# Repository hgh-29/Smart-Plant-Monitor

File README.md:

[README.pdf](https://github.com/user-attachments/files/24240184/README.pdf)

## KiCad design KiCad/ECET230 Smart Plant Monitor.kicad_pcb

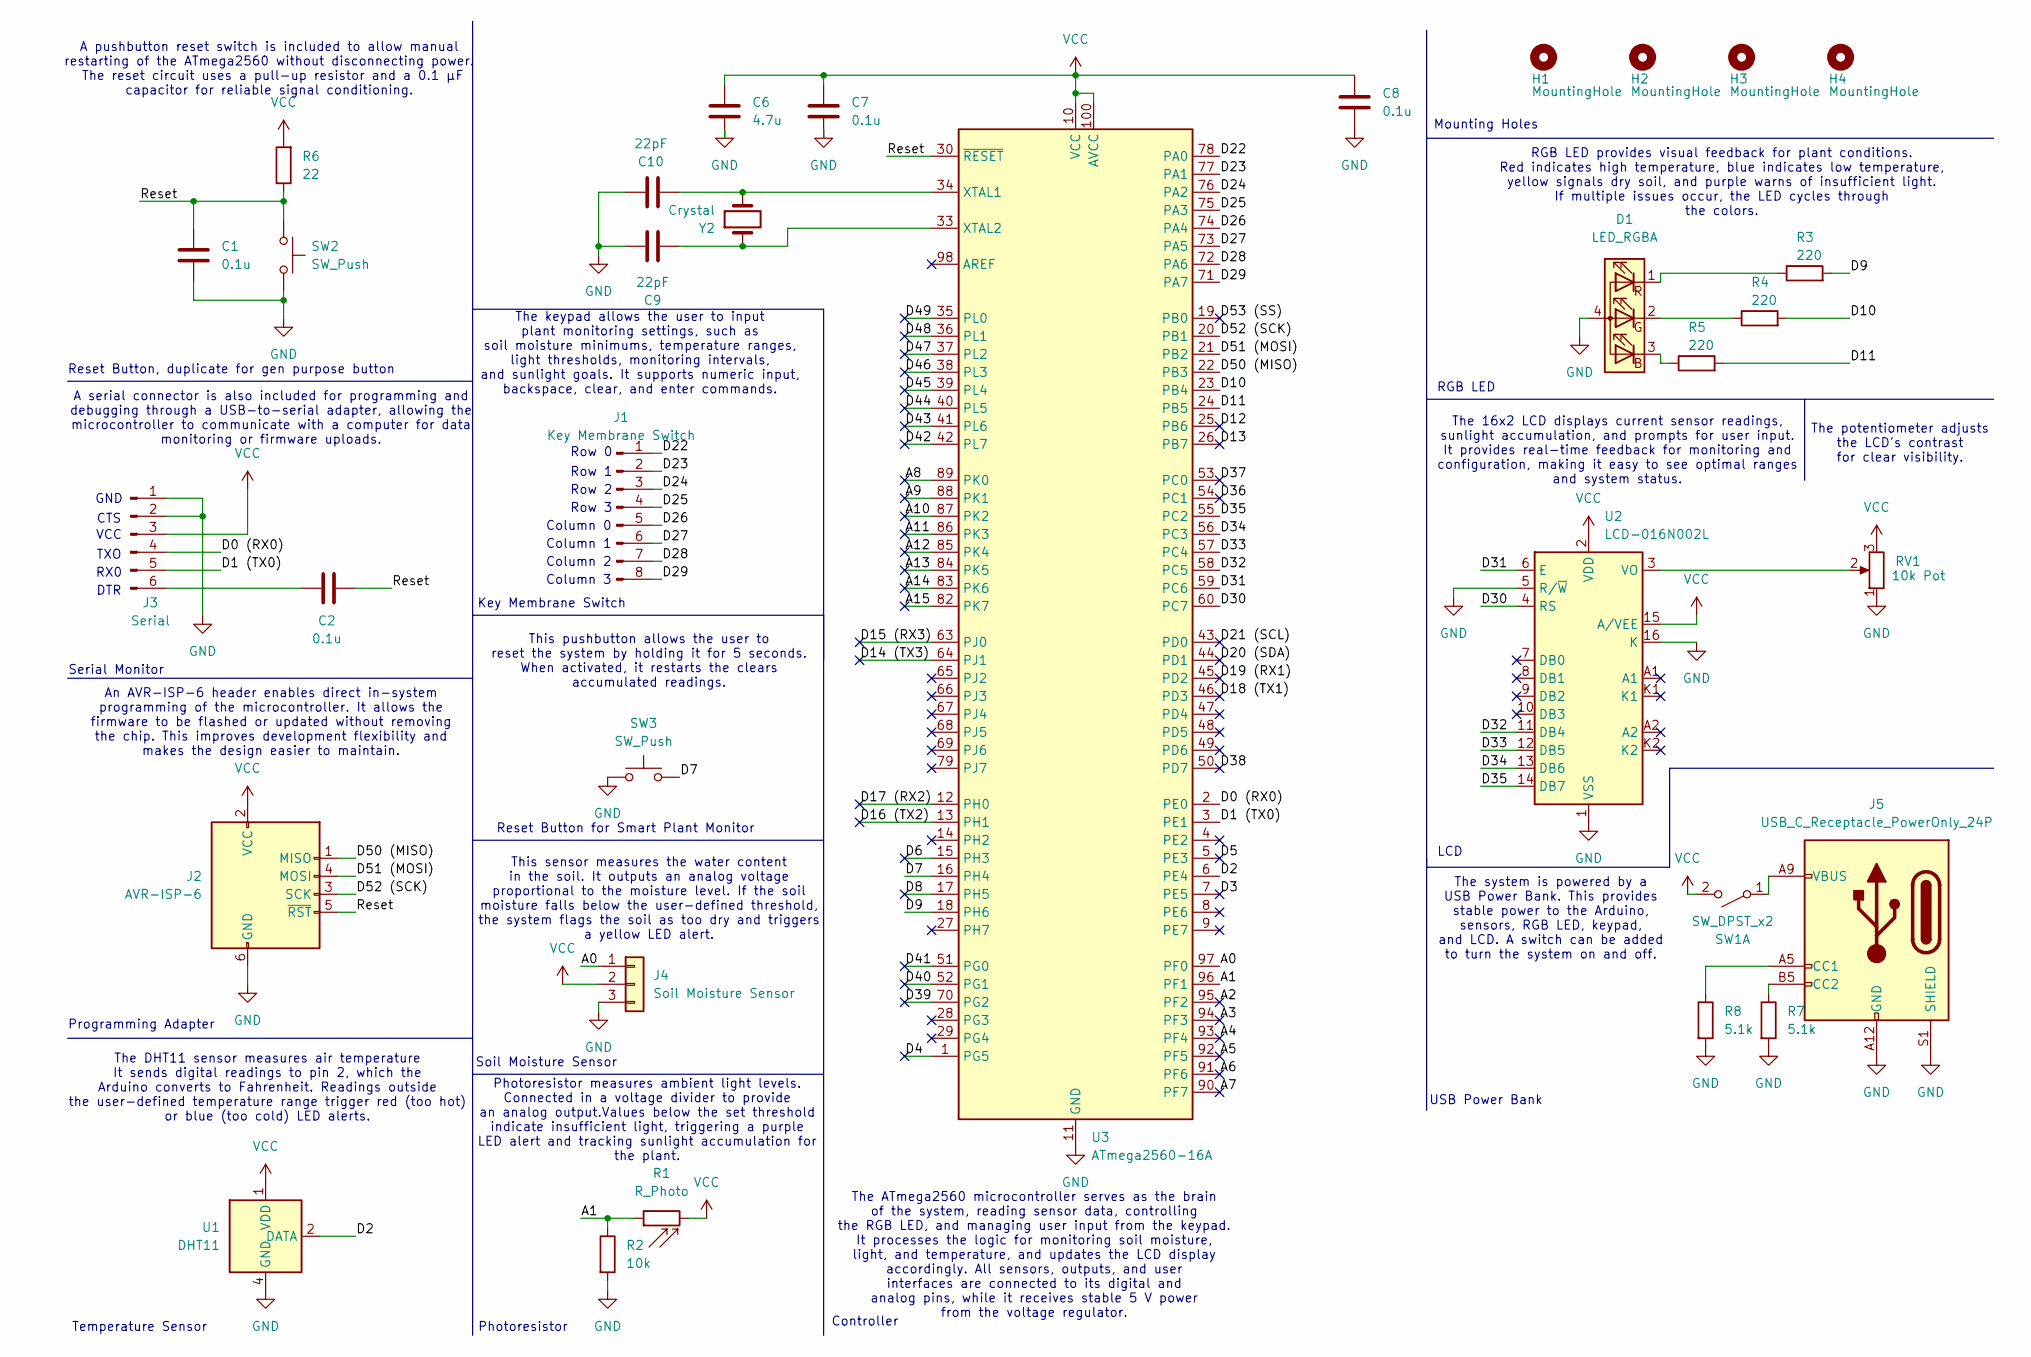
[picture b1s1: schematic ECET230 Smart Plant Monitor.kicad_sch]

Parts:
C1, C2, C7, C8: 0.1u; CP_Elec_3x5.3; MPN GRM033C71C104KE14D
C6: 4.7u; CP_Elec_3x5.3; MPN GRM035R60J475ME15D
C9, C10: 22pF; CP_Elec_3x5.3; MPN C0603C220J5GACTU
D1: LED_RGBA; LED_RGB_5050-6; MPN YSL-R596CR3G4B5C-C10
H1, H2, H3, H4: MountingHole; MountingHole_2.1mm
J1: Key Membrane Switch; PinHeader_1x08_P1.00mm_Vertical; MPN PPTC081LFBN-RC
J2: AVR-ISP-6; Tag-Connect_TC2030-IDC-FP_2x03_P1.27mm_Vertical; MPN SFH11-NBPC-D03-ST-BK
J3: Serial; PinSocket_1x06_P1.00mm_Vertical_SMD_Pin1Right; MPN OSTOQ063250
J4: Soil Moisture Sensor; PinSocket_1x03_P2.54mm_Horizontal; MPN PPPC031LGBN-RC
J5: USB_C_Receptacle_PowerOnly_24P; USB_C_Receptacle_GCT_USB4085; MPN USB4125-GF-A
R1: R_Photo; R_Axial_DIN0309_L9.0mm_D3.2mm_P12.70mm_Horizontal; MPN PDV-P8103
R2: 10k; R_Axial_DIN0309_L9.0mm_D3.2mm_P12.70mm_Horizontal; MPN CF14JT10K0
R3, R4, R5: 220; R_Axial_DIN0309_L9.0mm_D3.2mm_P12.70mm_Horizontal; MPN CF14JT220R
R6: 22; R_Axial_DIN0207_L6.3mm_D2.5mm_P10.16mm_Horizontal; MPN CF14JT22R0
R7, R8: 5.1k; R_Axial_DIN0207_L6.3mm_D2.5mm_P10.16mm_Horizontal; MPN CF14JT5K10
RV1: 10k Pot; Potentiometer_Bourns_3266P_Horizontal; MPN PV36W103C01B00
SW1: SW_DPST_x2; SW_DIP_SPSTx01_Slide_Copal_CHS-01A_W5.08mm_P1.27mm_JPin; MPN JS202011CQN
SW2, SW3: SW_Push; SW_PUSH-12mm_Wuerth-430476085716; MPN Y41A00521FPLFS
U1: DHT11; Aosong_DHT11_5.5x12.0_P2.54mm; MPN 386
U2: LCD-016N002L; MPN HD44780U (LCD-II)
U3: ATmega2560-16A; TQFP-100_14x14mm_P0.5mm; MPN ATMEGA2560-16AU
Y2: Crystal; Crystal_AT310_D3.0mm_L10.0mm_Horizontal; MPN ABS07-32.768KHZ-T

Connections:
/A0: J4.1, U3.97 (PF0)
/A1: R1.1, R2.1, U3.96 (PF1)
/A2: U3.95 (PF2)
/A3: U3.94 (PF3)
/A4: U3.93 (PF4)
/A5: U3.92 (PF5)
/A6: U3.91 (PF6)
/A7: U3.90 (PF7)
/A8: U3.89 (PK0)
/A9: U3.88 (PK1)
/A10: U3.87 (PK2)
/A11: U3.86 (PK3)
/A12: U3.85 (PK4)
/A13: U3.84 (PK5)
/A14: U3.83 (PK6)
/A15: U3.82 (PK7)
/D0 (RX0): J3.4, U3.2 (PE0)
/D1 (TX0): J3.5, U3.3 (PE1)
/D2: U1.2 (DATA), U3.6 (PE4)
/D3: U3.7 (PE5)
/D4: U3.1 (PG5)
/D5: U3.5 (PE3)
/D6: U3.15 (PH3)
/D7: SW3.2, U3.16 (PH4)
/D8: U3.17 (PH5)
/D9: R3.2, U3.18 (PH6)
/D10: R4.2, U3.23 (PB4)
/D11: R5.2, U3.24 (PB5)
/D12: U3.25 (PB6)
/D13: U3.26 (PB7)
/D14 (TX3): U3.64 (PJ1)
/D15 (RX3): U3.63 (PJ0)
/D16 (TX2): U3.13 (PH1)
/D17 (RX2): U3.12 (PH0)
/D18 (TX1): U3.46 (PD3)
/D19 (RX1): U3.45 (PD2)
/D20 (SDA): U3.44 (PD1)
/D21 (SCL): U3.43 (PD0)
/D22: J1.1, U3.78 (PA0)
/D23: J1.2, U3.77 (PA1)
/D24: J1.3, U3.76 (PA2)
/D25: J1.4, U3.75 (PA3)
/D26: J1.5, U3.74 (PA4)
/D27: J1.6, U3.73 (PA5)
/D28: J1.7, U3.72 (PA6)
/D29: J1.8, U3.71 (PA7)
/D30: U2.4 (RS), U3.60 (PC7)
/D31: U2.6 (E), U3.59 (PC6)
/D32: U2.11 (DB4), U3.58 (PC5)
/D33: U2.12 (DB5), U3.57 (PC4)
/D34: U2.13 (DB6), U3.56 (PC3)
/D35: U2.14 (DB7), U3.55 (PC2)
/D36: U3.54 (PC1)
/D37: U3.53 (PC0)
/D38: U3.50 (PD7)
/D39: U3.70 (PG2)
/D40: U3.52 (PG1)
/D41: U3.51 (PG0)
/D42: U3.42 (PL7)
/D43: U3.41 (PL6)
/D44: U3.40 (PL5)
/D45: U3.39 (PL4)
/D46: U3.38 (PL3)
/D47: U3.37 (PL2)
/D48: U3.36 (PL1)
/D49: U3.35 (PL0)
/D50 (MISO): J2.1 (MISO), U3.22 (PB3)
/D51 (MOSI): J2.4 (MOSI), U3.21 (PB2)
/D52 (SCK): J2.3 (SCK), U3.20 (PB1)
/D53 (SS): U3.19 (PB0)
/Reset: C1.1, C2.1, J2.5 (~RST), R6.1, SW2.1, U3.30 (~RESET)
GND: C1.2, C6.2, C7.2, C8.2, C9.1, C10.1, D1.4 (A), J2.6 (GND), J3.1, J3.2, J4.3, J5.A1 (GND), J5.A12 (GND), J5.B1 (GND), J5.B12 (GND), J5.S1 (SHIELD), R2.2, R7.2, R8.2, RV1.1, SW2.2, SW3.1, U1.4 (GND), U2.1 (VSS), U2.5 (R/~W), U2.16 (K), U3.11 (GND), U3.32 (GND), U3.62 (GND), U3.81 (GND), U3.99 (GND)
unnamed: D1.3 (BK), R5.1
unnamed: D1.2 (GK), R4.1
unnamed: D1.1 (RK), R3.1
unnamed: C2.2, J3.6
unnamed: J5.A5 (CC1), R8.1
unnamed: J5.B5 (CC2), R7.1
unnamed: J5.A4 (VBUS), J5.A9 (VBUS), J5.B4 (VBUS), J5.B9 (VBUS), SW1.1 (A)
unnamed: RV1.2, U2.3 (VO)
unnamed: C10.2, U3.34 (XTAL1), Y2.2
unnamed: C9.2, U3.33 (XTAL2), Y2.1
VCC: C6.1, C7.1, C8.1, J2.2 (VCC), J3.3, J4.2, R1.2, R6.2, RV1.3, SW1.2 (B), U1.1 (VDD), U2.2 (VDD), U2.15 (A/VEE), U3.10 (VCC), U3.31 (VCC), U3.61 (VCC), U3.80 (VCC), U3.100 (AVCC)

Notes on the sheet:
The 16x2 LCD displays current sensor readings, sunlight accumulation, and prompts for user input. It provides real-time feedback for monitoring and configuration, making it easy to see optimal ranges and system status.
An AVR-ISP-6 header enables direct in-system programming of the microcontroller. It allows the firmware to be flashed or updated without removing the chip. This improves development flexibility and makes the design easier to maintain.
GND
Programming Adapter
LCD
RGB LED provides visual feedback for plant conditions. Red indicates high temperature, blue indicates low temperature, yellow signals dry soil, and purple warns of insufficient light. If multiple issues occur, the LED cycles through the colors.
Serial Monitor
The ATmega2560 microcontroller serves as the brain of the system, reading sensor data, controlling the RGB LED, and managing user input from the keypad. It processes the logic for monitoring soil moisture, light, and temperature, and updates the LCD display accordingly. All sensors, outputs, and us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
A pushbutton reset switch is included to allow manual restarting of the ATmega2560 without disconnecting power. The reset circuit uses a pull-up resistor and a 0.1 µF capacitor for reliable signal conditioning.
VCC
RX0
Controller
Temperature Sensor
Photoresistor measures ambient light levels. Connected in a voltage divider to provide an analog output.Values below the set threshold indicate insufficient light, triggering a purple LED alert and tracking sunlight accumulation for the plant.
The DHT11 sensor measures air temperature It sends digital readings to pin 2, which the Arduino converts to Fahrenheit. Readings outside the user-defined temperature range trigger red (too hot) or blue (too cold) LED alerts.
Mounting Holes
Photoresistor
Soil Moisture Sensor
The potentiometer adjusts the LCD's contrast for clear visibility.
Reset Button for Smart Plant Monitor
USB Power Bank
RGB LED
Column 1
The keypad allows the user to input plant monitoring settings, such as soil moisture minimums, temperature ranges, light thresholds, monitoring intervals, and sunlight goals. It supports numeric input, backspace, clear, and enter commands.
Key Membrane Switch
The system is powered by a USB Power Bank. This provides stable power to the Arduino, sensors, RGB LED, keypad, and LCD. A switch can be added to turn the system on and off.
DTR
Row 0
Column 3
Reset Button, duplicate for gen purpose button
Column 2
This pushbutton allows the user to reset the system by holding it for 5 seconds. When activated, it restarts the clears accumulated readings.
Row 2
Row 3
This sensor measures the water content in the soil. It outputs an analog voltage proportional to the moisture level. If the soil moisture falls below the user-defined threshold, the system flags the soil as too dry and triggers a yellow LED alert.
Row 1
TXO
A serial connector is also included for programming and debugging through a USB-to-serial adapter, allowing the microcontroller to communicate with a computer for data monitoring or firmware uploads.
CTS
Column 0

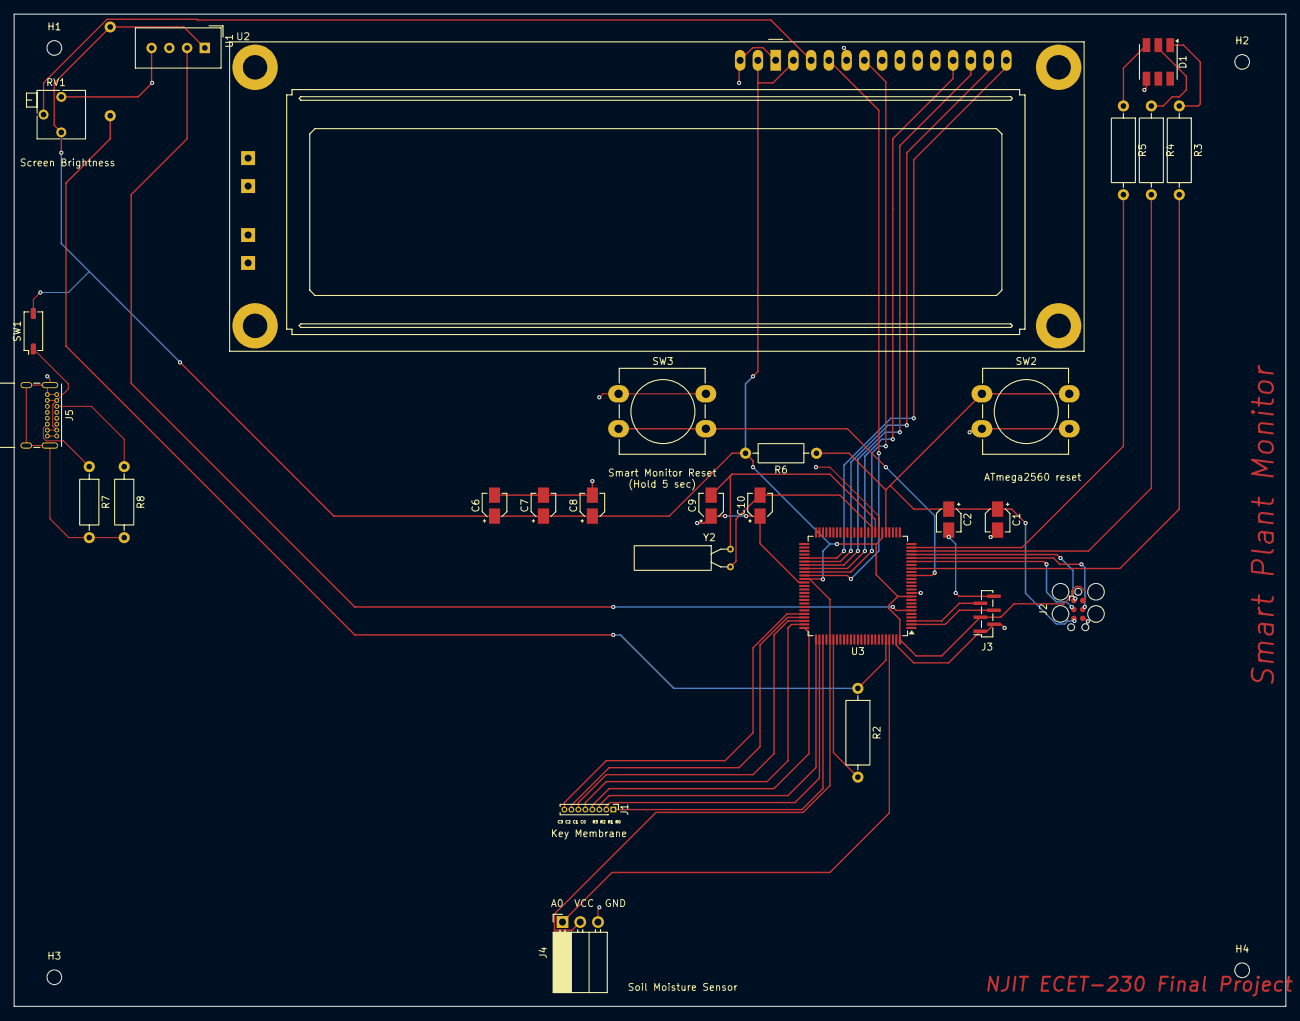
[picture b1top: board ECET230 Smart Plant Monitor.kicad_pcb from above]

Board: 2 copper layers, 182.0 x 142.0 mm, 33 parts (1 on the bottom side), 39 nets.

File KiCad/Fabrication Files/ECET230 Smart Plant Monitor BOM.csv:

"Id";"Designator";"Footprint";"Quantity";"Designation";"Supplier and ref";
1;"J4";"PinSocket_1x03_P2.54mm_Horizontal";1;"Soil Moisture Sensor";;;
2;"U1";"Aosong_DHT11_5.5x12.0_P2.54mm";1;"DHT11";;;
3;"SW1";"SW_DIP_SPSTx01_Slide_Copal_CHS-01A_W5.08mm_P1.27mm_JPin";1;"SW_DPST_x2";;;
4;"R3,R5,R4";"R_Axial_DIN0309_L9.0mm_D3.2mm_P12.70mm_Horizontal";3;"220";;;
5;"C2,C1,C7,C8";"CP_Elec_3x5.3";4;"0.1u";;;
6;"J5";"USB_C_Receptacle_GCT_USB4085";1;"USB_C_Receptacle_PowerOnly_24P";;;
7;"D1";"LED_RGB_5050-6";1;"LED_RGBA";;;
8;"C9,C10";"CP_Elec_3x5.3";2;"22pF";;;
9;"U2";"LCD-016N002L";1;"LCD-016N002L";;;
10;"R8,R7";"R_Axial_DIN0207_L6.3mm_D2.5mm_P10.16mm_Horizontal";2;"5.1k";;;
11;"Y2";"Crystal_AT310_D3.0mm_L10.0mm_Horizontal";1;"Crystal";;;
12;"SW2,SW3";"SW_PUSH-12mm_Wuerth-430476085716";2;"SW_Push";;;
13;"U3";"TQFP-100_14x14mm_P0.5mm";1;"ATmega2560-16A";;;
14;"J3";"PinSocket_1x06_P1.00mm_Vertical_SMD_Pin1Right";1;"Serial";;;
15;"R2";"R_Axial_DIN0309_L9.0mm_D3.2mm_P12.70mm_Horizontal";1;"10k";;;
16;"J2";"Tag-Connect_TC2030-IDC-FP_2x03_P1.27mm_Vertical";1;"AVR-ISP-6";;;
17;"C6";"CP_Elec_3x5.3";1;"4.7u";;;
18;"J1";"PinHeader_1x08_P1.00mm_Vertical";1;"Key Membrane Switch";;;
19;"R6";"R_Axial_DIN0207_L6.3mm_D2.5mm_P10.16mm_Horizontal";1;"22";;;
20;"RV1";"Potentiometer_Bourns_3266P_Horizontal";1;"10k Pot";;;
21;"R1";"R_Axial_DIN0309_L9.0mm_D3.2mm_P12.70mm_Horizontal";1;"R_Photo";;;

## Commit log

2025-09-23 Create Design Decisions
2025-09-23 Update Design Decisions
2025-09-23 Create f
2025-09-24 README.md
2025-12-18 Add link to README.pdf in README.md
2025-12-18 Add installation guide for KiCad
    Added installation instructions for KiCad on Windows and macOS.
2025-12-18 Add download link for KiCad installation
    Updated installation instructions for KiCad with a download link.
2025-12-18 Add instructions to download Arduino IDE
2025-12-18 Document project contents in repository
    Added a list of documents included in the repository.
2025-12-18 Add midterm and final project presentation sections
2025-12-18 Update project document list with block diagram
2025-12-18 Create Fabrication Files
2025-12-18 Create c
2025-12-18 Create c
2025-12-18 Create g
2025-12-18 Create a
